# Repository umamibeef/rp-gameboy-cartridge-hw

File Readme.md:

# HW repository for the Croco Cartridges
The files come as is. I used them to order the cartridges, but while ordering yourself you should of course check yourself if everything is correct.

## Revisions
See [CHANGELOG.md](CHANGELOG.md) for what changed in each board revision.

## License
CERN Open Hardware Licence Version 2 - Permissive

## What you should look after while ordering
The PCB thickness should be 0.8mm. This will make perfect contact with the Gameboy if the PCB is within a cartridge casing.

You should order with ENIG (electroless nickel immersion gold) plating. While the cartridge will work with HASL you will getter contact with ENIG and it is less prone to wearing down.

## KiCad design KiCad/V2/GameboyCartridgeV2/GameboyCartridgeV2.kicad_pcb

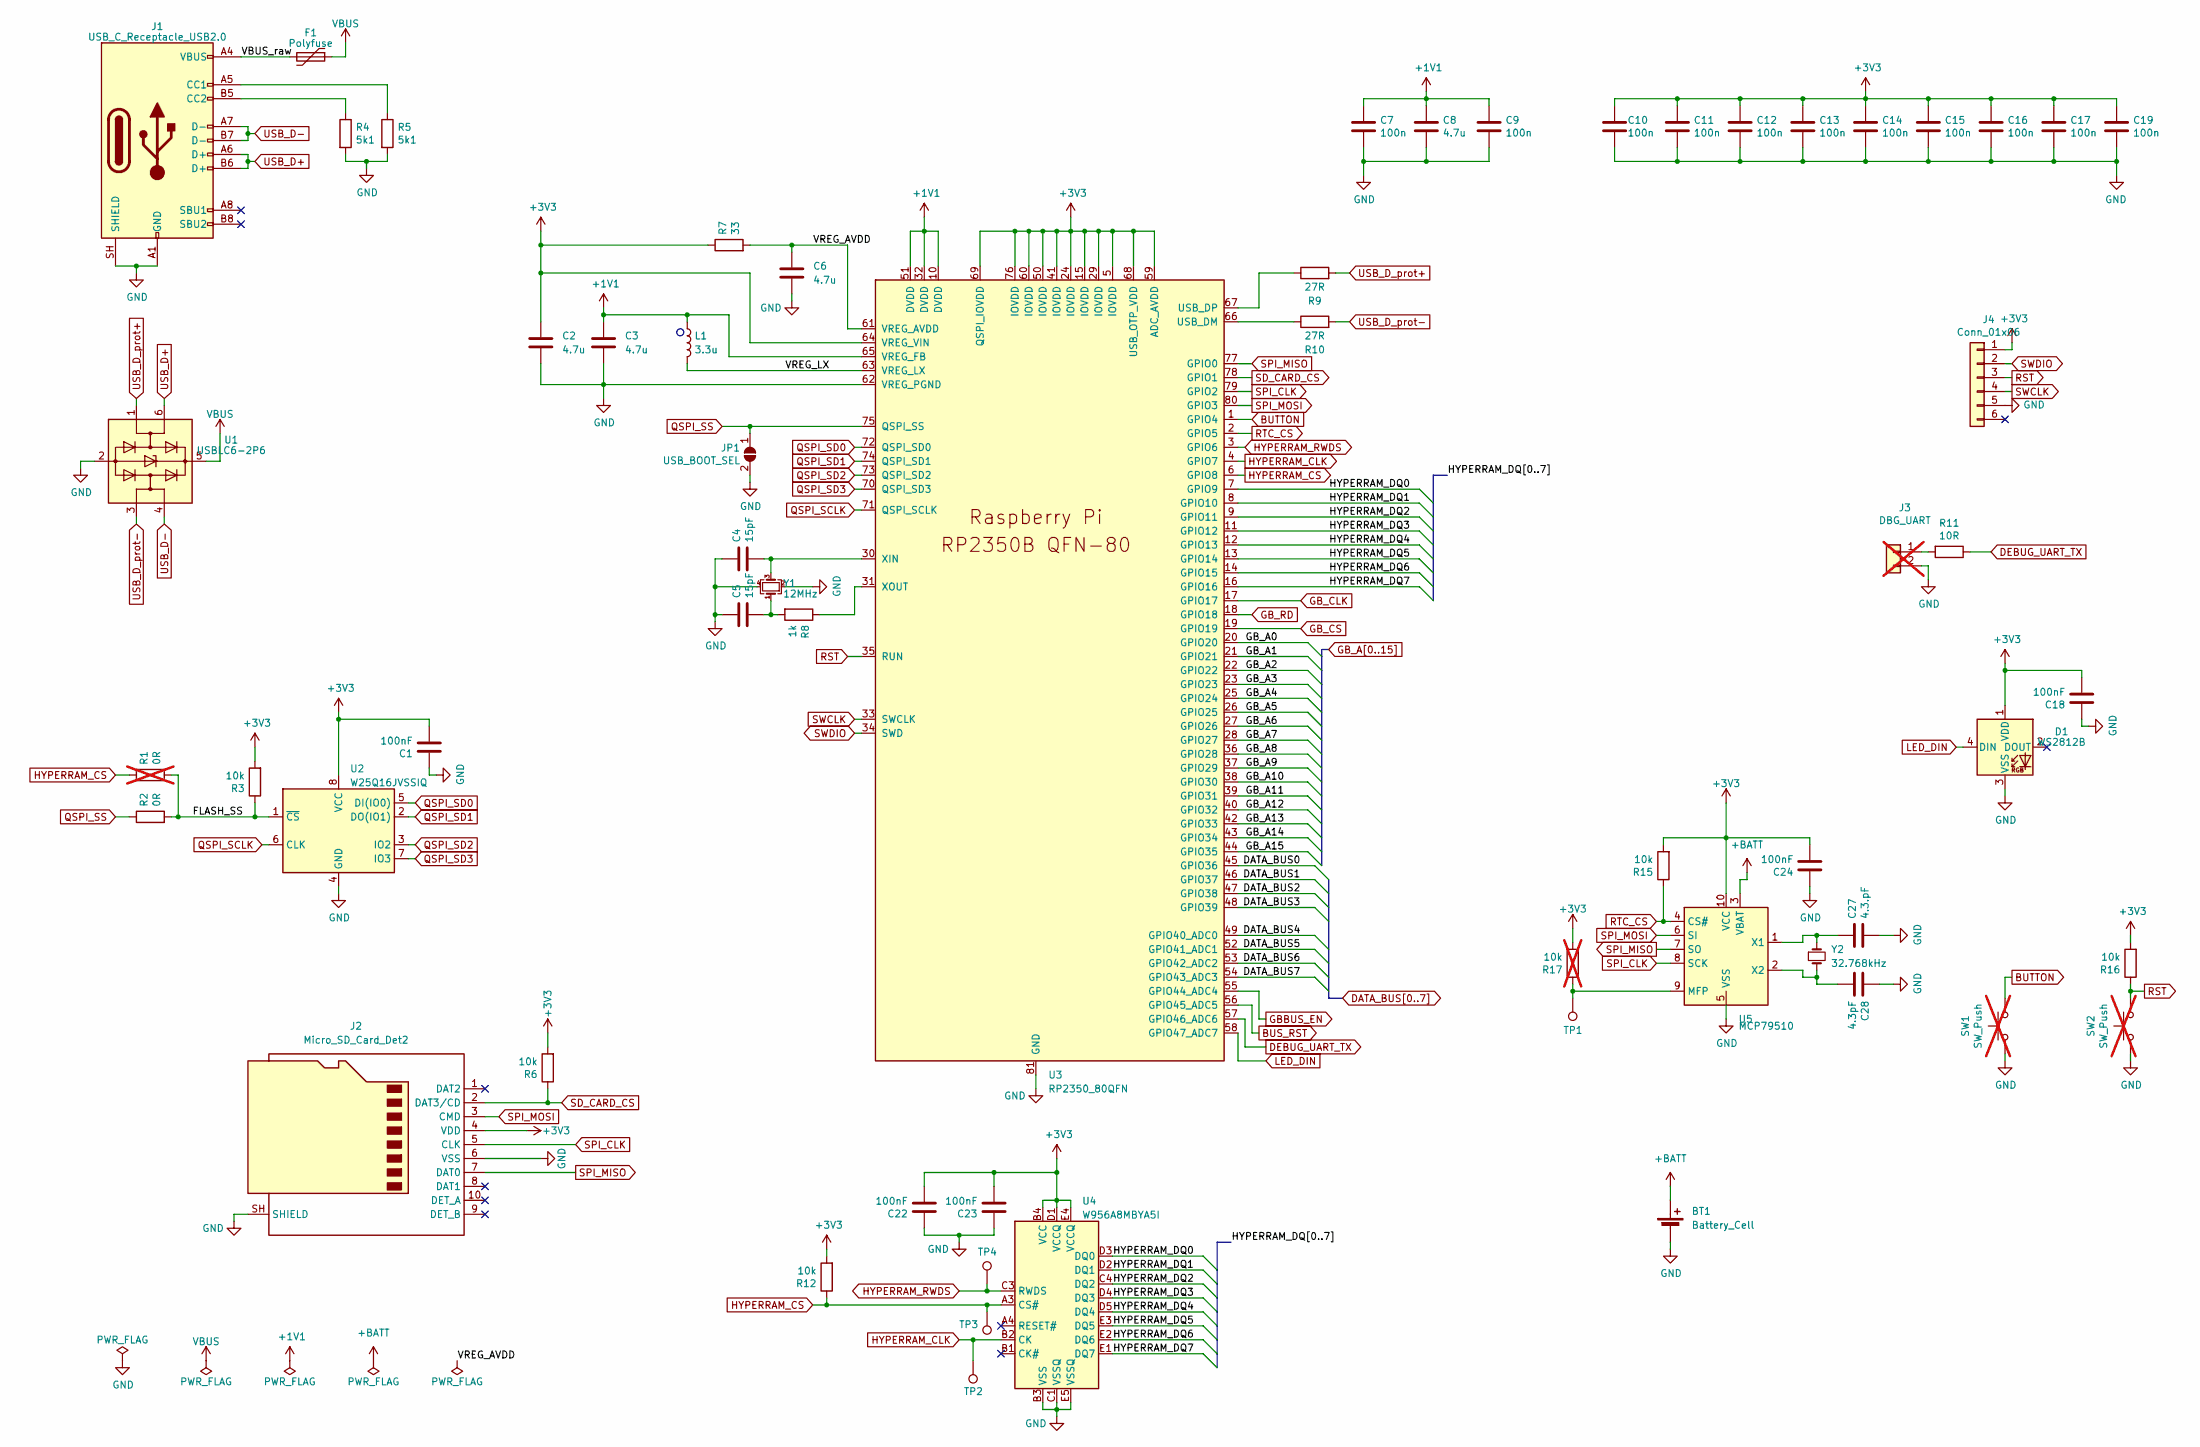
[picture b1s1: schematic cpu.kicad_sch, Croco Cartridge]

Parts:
BT1: Battery_Cell; BatteryHolder_Keystone_3000_1x12mm; LCSC C6997853
C1, C18, C22, C23, C24: 100nF; C_0603_1608Metric
C2, C3: 4.7u; C_0402_1005Metric_small_pads
C4, C5: 15pF; C_0603_1608Metric; LCSC C1644
C6, C8: 4.7u; C_0402_1005Metric
C7, C9, C10, C11, C12, C13, C14, C15, C16, C17, C19: 100n; C_0402_1005Metric
C27: 4.3.pF; C_0603_1608Metric; LCSC C1644
C28: 4.3pF; C_0603_1608Metric; LCSC C1644
D1: WS2812B; LED_WS2812B_PLCC4_5.0x5.0mm_P3.2mm; LCSC C2761795
F1: Polyfuse; Fuse_1206_3216Metric; LCSC C2649911
J1: USB_C_Receptacle_USB2.0; USB_C_Receptacle_GCT_USB4105-xx-A_16P_TopMnt_Horizontal; LCSC C2927037
J2: Micro_SD_Card_Det2; microSD_HC_Hirose_DM3D-SF; LCSC C719027
J3: DBG_UART; PinHeader_1x02_P2.54mm_Horizontal; not fitted
J4: Conn_01x06; Tag-Connect_TC2030-IDC-NL_2x03_P1.27mm_Vertical
JP1: USB_BOOT_SEL; SolderJumper-2_P1.3mm_Open_RoundedPad1.0x1.5mm
L1: 3.3u; L_pol_2016; LCSC C42411119
R1: 0R; R_0603_1608Metric; not fitted
R2: 0R; R_0603_1608Metric
R3, R6, R12, R15, R16: 10k; R_0603_1608Metric
R4, R5: 5k1; R_0603_1608Metric
R7: 33; R_0402_1005Metric
R8: 1k; R_0603_1608Metric
R9, R10: 27R; R_0603_1608Metric
R11: 10R; R_0603_1608Metric
R17: 10k; R_0603_1608Metric; not fitted
SW1: SW_Push; GameBoy_soft_button; not fitted
SW2: SW_Push; SW_SPST_PTS810; not fitted
TP1, TP2, TP3, TP4: TestPoint; TestPoint_Pad_D1.0mm
U1: USBLC6-2P6; SOT-666; LCSC C15999
U2: W25Q16JVSSIQ; SOIC-8_5.3x5.3mm_P1.27mm; LCSC C82317
U3: RP2350_80QFN; RP2350-QFN-80-1EP_10x10_P0.4mm_EP3.4x3.4mm_ThermalVias; LCSC C42415655
U4: W956A8MBYA5I; BGA25C100P5X5_800X600X120N; LCSC C5375118
U5: MCP79510; MSOP-10_3x3mm_P0.5mm; LCSC C627708
Y1: 12MHz; Crystal_SMD_TXC_7M-4Pin_3.2x2.5mm; LCSC C668845
Y2: 32.768kHz; Crystal_SMD_TXC_9HT11-2Pin_2.0x1.2mm; LCSC C97602

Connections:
+1V1: C3.1, C7.1, C8.1, C9.1, L1.1, U3.10 (DVDD), U3.32 (DVDD), U3.51 (DVDD), U3.65 (VREG_FB)
+3V3: C1.2, C2.1, C10.1, C11.1, C12.1, C13.1, C14.1, C15.1, C16.1, C17.1, C18.2, C19.1, C22.2, C23.2, C24.2, D1.1 (VDD), J2.4 (VDD_4), J4.1, R3.2, R6.2, R7.1, R12.2, R15.2, R16.2, R17.2, U2.8 (VCC), U3.5 (IOVDD), U3.15 (IOVDD), U3.24 (IOVDD), U3.29 (IOVDD), U3.41 (IOVDD), U3.50 (IOVDD), U3.59 (ADC_AVDD), U3.60 (IOVDD), U3.64 (VREG_VIN), U3.68 (USB_OTP_VDD), U3.69 (QSPI_IOVDD), U3.76 (IOVDD), U4.B4 (VCC), U4.D1 (VCCQ), U4.E4 (VCCQ), U5.10 (VCC); also elsewhere on the board
+BATT: BT1.1 (+), U5.3 (VBAT)
/CPU/FLASH_SS: R1.2, R2.2, R3.1, U2.1 (~CS)
/CPU/HYPERRAM_DQ0: U3.7 (GPIO9), U4.D3 (DQ0)
/CPU/HYPERRAM_DQ1: U3.8 (GPIO10), U4.D2 (DQ1)
/CPU/HYPERRAM_DQ2: U3.9 (GPIO11), U4.C4 (DQ2)
/CPU/HYPERRAM_DQ3: U3.11 (GPIO12), U4.D4 (DQ3)
/CPU/HYPERRAM_DQ4: U3.12 (GPIO13), U4.D5 (DQ4)
/CPU/HYPERRAM_DQ5: U3.13 (GPIO14), U4.E3 (DQ5)
/CPU/HYPERRAM_DQ6: U3.14 (GPIO15), U4.E2 (DQ6)
/CPU/HYPERRAM_DQ7: U3.16 (GPIO16), U4.E1 (DQ7)
/CPU/VBUS_raw: F1.2, J1.A4 (VBUS_A4), J1.A9 (VBUS_A9), J1.B4 (VBUS_B4), J1.B9 (VBUS_B9)
/CPU/VREG_AVDD: C6.1, R7.2, U3.61 (VREG_AVDD)
/CPU/VREG_LX: L1.2, U3.63 (VREG_LX)
BUS_RST: U3.56 (GPIO45_ADC5); also elsewhere on the board
BUTTON: SW1.1, U3.1 (GPIO4)
DATA_BUS0: U3.45 (GPIO36); also elsewhere on the board
DATA_BUS1: U3.46 (GPIO37); also elsewhere on the board
DATA_BUS2: U3.47 (GPIO38); also elsewhere on the board
DATA_BUS3: U3.48 (GPIO39); also elsewhere on the board
DATA_BUS4: U3.49 (GPIO40_ADC0); also elsewhere on the board
DATA_BUS5: U3.52 (GPIO41_ADC1); also elsewhere on the board
DATA_BUS6: U3.53 (GPIO42_ADC2); also elsewhere on the board
DATA_BUS7: U3.54 (GPIO43_ADC3); also elsewhere on the board
DEBUG_UART_TX: R11.1, U3.57 (GPIO46_ADC6)
GBBUS_EN: U3.55 (GPIO44_ADC4); also elsewhere on the board
GB_A0: U3.20 (GPIO20); also elsewhere on the board
GB_A1: U3.21 (GPIO21); also elsewhere on the board
GB_A2: U3.22 (GPIO22); also elsewhere on the board
GB_A3: U3.23 (GPIO23); also elsewhere on the board
GB_A4: U3.25 (GPIO24); also elsewhere on the board
GB_A5: U3.26 (GPIO25); also elsewhere on the board
GB_A6: U3.27 (GPIO26); also elsewhere on the board
GB_A7: U3.28 (GPIO27); also elsewhere on the board
GB_A8: U3.36 (GPIO28); also elsewhere on the board
GB_A9: U3.37 (GPIO29); also elsewhere on the board
GB_A10: U3.38 (GPIO30); also elsewhere on the board
GB_A11: U3.39 (GPIO31); also elsewhere on the board
GB_A12: U3.40 (GPIO32); also elsewhere on the board
GB_A13: U3.42 (GPIO33); also elsewhere on the board
GB_A14: U3.43 (GPIO34); also elsewhere on the board
GB_A15: U3.44 (GPIO35); also elsewhere on the board
GB_CLK: U3.17 (GPIO17); also elsewhere on the board
GB_CS: U3.19 (GPIO19); also elsewhere on the board
GB_RD: U3.18 (GPIO18); also elsewhere on the board
GND: BT1.2 (-), C1.1, C2.2, C3.2, C4.1, C5.1, C6.2, C7.2, C8.2, C9.2, C10.2, C11.2, C12.2, C13.2, C14.2, C15.2, C16.2, C17.2, C18.1, C19.2, C22.1, C23.1, C24.1, C27.2, C28.1, D1.3 (VSS), J1.A1 (GND_A1), J1.A12 (GND_A12), J1.B1 (GND_B1), J1.B12 (GND_B12), J1.SH (SHIELD_S1), J2.6 (VSS_6), J2.SH (SHIELD_11), J3.2, J4.5, JP1.2 (B), R4.2, R5.2, SW1.2, SW2.2, U1.2 (GND), U2.4 (GND), U3.62 (VREG_PGND), U3.81 (GND), U4.B3 (VSS), U4.C1 (VSSQ), U4.E5 (VSSQ), U5.5 (VSS), Y1.2, Y1.4; also elsewhere on the board
HYPERRAM_CLK: TP2.1 (1_1), U3.4 (GPIO7), U4.B2 (CK)
HYPERRAM_CS: R1.1, R12.1, TP3.1 (1_1), U3.6 (GPIO8), U4.A3 (CS#)
HYPERRAM_RWDS: TP4.1 (1_1), U3.3 (GPIO6), U4.C3 (RWDS)
LED_DIN: D1.4 (DIN), U3.58 (GPIO47_ADC7)
unnamed: C5.2, R8.2, Y1.1
unnamed: J1.A5 (CC1_A5), R5.1
unnamed: J1.B5 (CC2_B5), R4.1
unnamed: J3.1, R11.2
unnamed: R10.1, U3.66 (USB_DM)
unnamed: R9.1, U3.67 (USB_DP)
unnamed: C4.2, U3.30 (XIN), Y1.3
unnamed: R8.1, U3.31 (XOUT)
unnamed: R17.1, TP1.1 (1_1), U5.9 (MFP)
unnamed: C27.1, U5.1 (X1), Y2.1
unnamed: C28.2, U5.2 (X2), Y2.2
QSPI_SCLK: U2.6 (CLK), U3.71 (QSPI_SCLK)
QSPI_SD0: U2.5 (DI(IO0)), U3.72 (QSPI_SD0)
QSPI_SD1: U2.2 (DO(IO1)), U3.74 (QSPI_SD1)
QSPI_SD2: U2.3 (IO2), U3.73 (QSPI_SD2)
QSPI_SD3: U2.7 (IO3), U3.70 (QSPI_SD3)
QSPI_SS: JP1.1 (A), R2.1, U3.75 (QSPI_SS)
RST: J4.3, R16.1, SW2.1, U3.35 (RUN)
RTC_CS: R15.1, U3.2 (GPIO5), U5.4 (CS#)
SD_CARD_CS: J2.2 (DAT3/CD_2), R6.1, U3.78 (GPIO1)
SPI_CLK: J2.5 (CLK_5), U3.79 (GPIO2), U5.8 (SCK)
SPI_MISO: J2.7 (DAT0_7), U3.77 (GPIO0), U5.7 (SO)
SPI_MOSI: J2.3 (CMD_3), U3.80 (GPIO3), U5.6 (SI)
SWCLK: J4.4, U3.33 (SWCLK)
SWDIO: J4.2, U3.34 (SWD)
USB_D+: J1.A6 (D+_A6), J1.B6 (D+_B6), U1.6 (I/O1)
USB_D-: J1.A7 (D-_A7), J1.B7 (D-_B7), U1.4 (I/O2)
USB_D_prot+: R9.2, U1.1 (I/O1)
USB_D_prot-: R10.2, U1.3 (I/O2)
VBUS: F1.1, U1.5 (VBUS); also elsewhere on the board

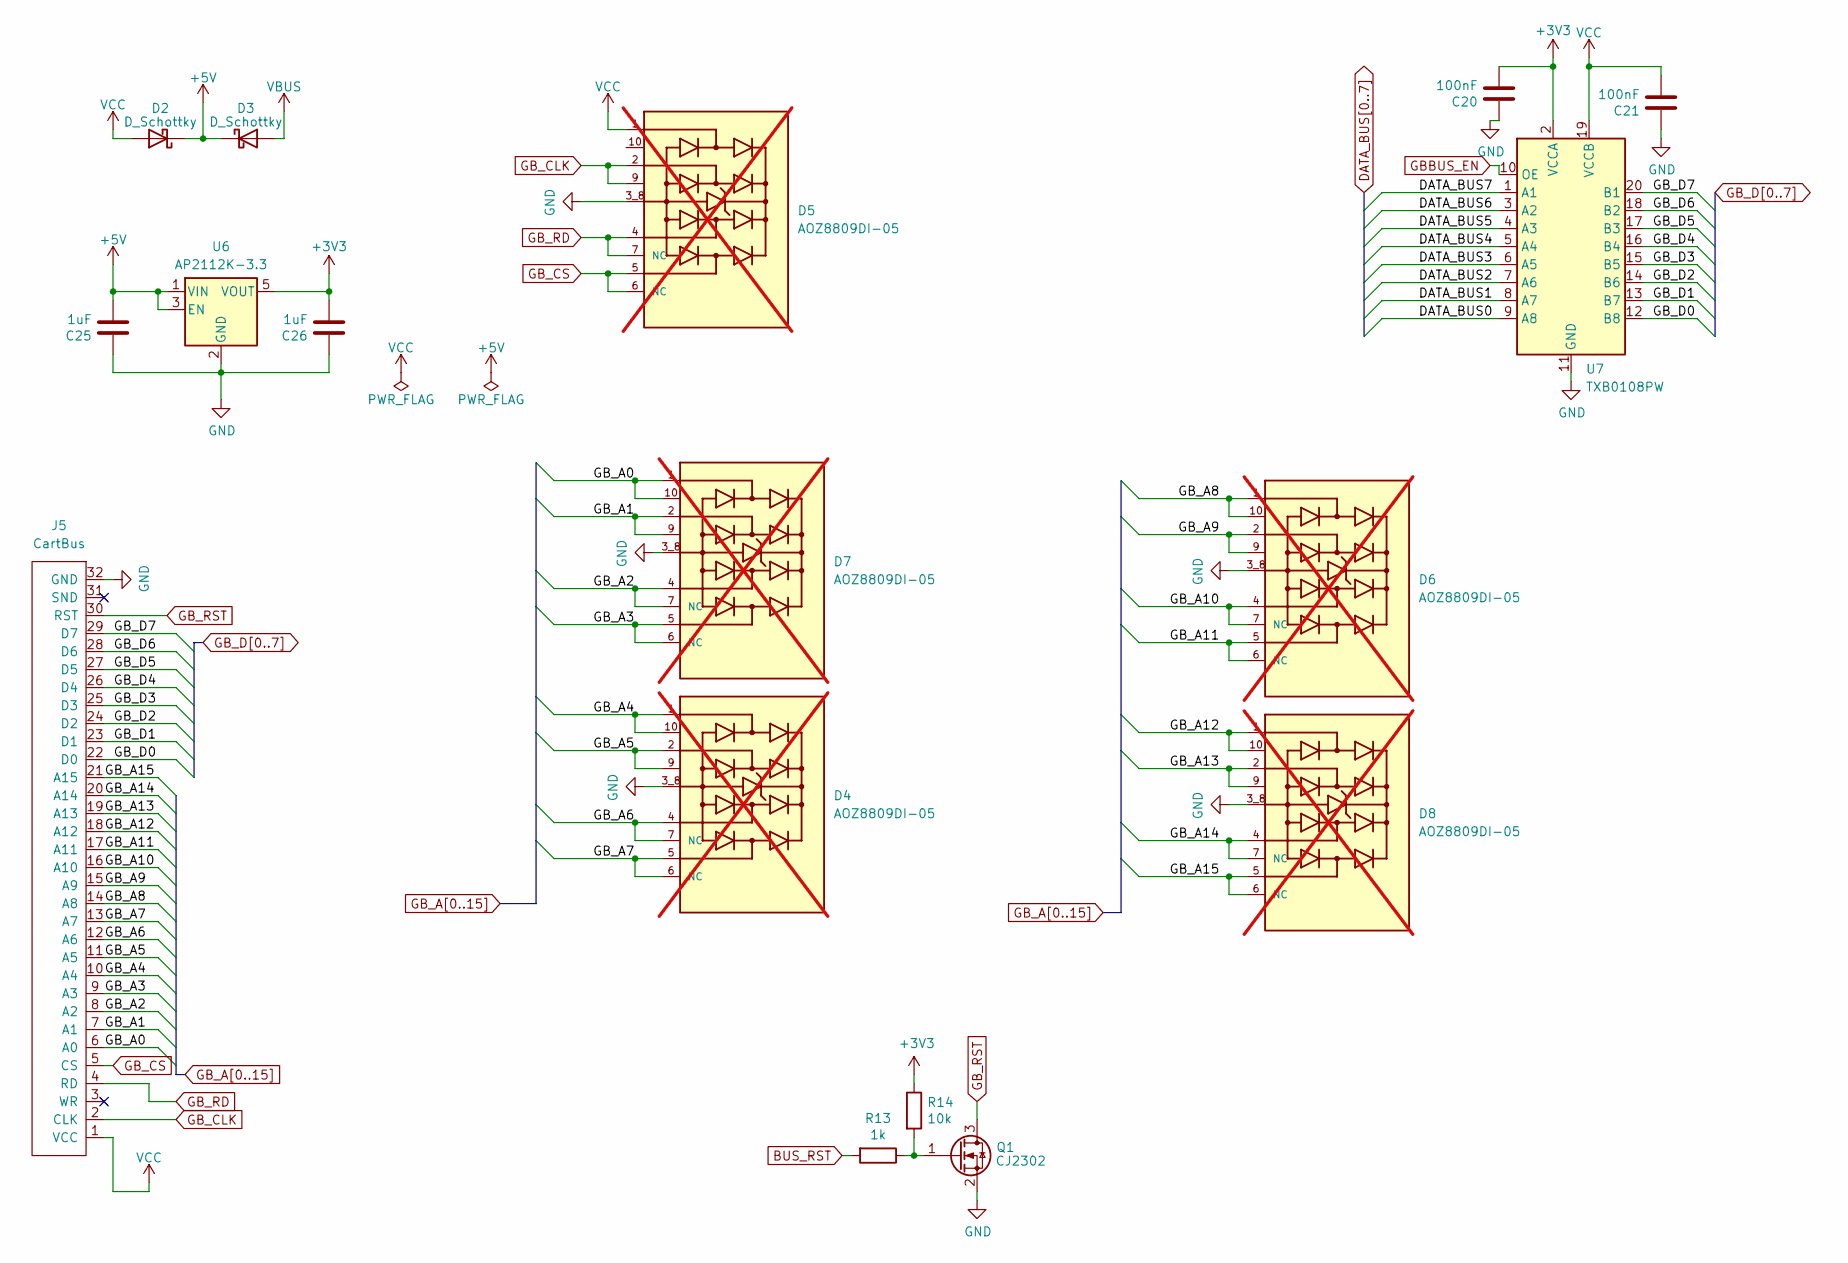
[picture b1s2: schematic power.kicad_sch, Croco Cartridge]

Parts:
C20, C21: 100nF; C_0603_1608Metric
C25, C26: 1uF; C_0603_1608Metric
D2, D3: D_Schottky; D_SOD-123F; LCSC C669022
D4, D5, D6, D7, D8: AOZ8809DI-05; TVS_AOZ8809DI-05; PARTREV Rev. 7.0; not fitted
J5: CartBus; GameBoy_Cartridge_EdgeConnector
Q1: CJ2302; SOT-23; LCSC C8548
R13: 1k; R_0603_1608Metric
R14: 10k; R_0603_1608Metric
U6: AP2112K-3.3; SOT-23-5; LCSC C51118
U7: TXB0108PW; TSSOP-20_4.4x6.5mm_P0.65mm; LCSC C53406

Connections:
+3V3: C20.2, C26.2, R14.1, U6.5 (VOUT), U7.2 (VCCA); also elsewhere on the board
+5V: C25.2, D2.1 (K), D3.1 (K), U6.1 (VIN), U6.3 (EN)
BUS_RST: R13.2; also elsewhere on the board
DATA_BUS0: U7.9 (A8); also elsewhere on the board
DATA_BUS1: U7.8 (A7); also elsewhere on the board
DATA_BUS2: U7.7 (A6); also elsewhere on the board
DATA_BUS3: U7.6 (A5); also elsewhere on the board
DATA_BUS4: U7.5 (A4); also elsewhere on the board
DATA_BUS5: U7.4 (A3); also elsewhere on the board
DATA_BUS6: U7.3 (A2); also elsewhere on the board
DATA_BUS7: U7.1 (A1); also elsewhere on the board
GBBUS_EN: U7.10 (OE); also elsewhere on the board
GB_A0: D7.1, D7.10, J5.6 (A0); also elsewhere on the board
GB_A1: D7.2, D7.9, J5.7 (A1); also elsewhere on the board
GB_A2: D7.4, D7.7 (NC), J5.8 (A2); also elsewhere on the board
GB_A3: D7.5, D7.6 (NC), J5.9 (A3); also elsewhere on the board
GB_A4: D4.1, D4.10, J5.10 (A4); also elsewhere on the board
GB_A5: D4.2, D4.9, J5.11 (A5); also elsewhere on the board
GB_A6: D4.4, D4.7 (NC), J5.12 (A6); also elsewhere on the board
GB_A7: D4.5, D4.6 (NC), J5.13 (A7); also elsewhere on the board
GB_A8: D6.1, D6.10, J5.14 (A8); also elsewhere on the board
GB_A9: D6.2, D6.9, J5.15 (A9); also elsewhere on the board
GB_A10: D6.4, D6.7 (NC), J5.16 (A10); also elsewhere on the board
GB_A11: D6.5, D6.6 (NC), J5.17 (A11); also elsewhere on the board
GB_A12: D8.1, D8.10, J5.18 (A12); also elsewhere on the board
GB_A13: D8.2, D8.9, J5.19 (A13); also elsewhere on the board
GB_A14: D8.4, D8.7 (NC), J5.20 (A14); also elsewhere on the board
GB_A15: D8.5, D8.6 (NC), J5.21 (A15); also elsewhere on the board
GB_CLK: D5.2, D5.9, J5.2 (CLK~); also elsewhere on the board
GB_CS: D5.5, D5.6 (NC), J5.5 (CS); also elsewhere on the board
GB_D0: J5.22 (D0), U7.12 (B8)
GB_D1: J5.23 (D1), U7.13 (B7)
GB_D2: J5.24 (D2), U7.14 (B6)
GB_D3: J5.25 (D3), U7.15 (B5)
GB_D4: J5.26 (D4), U7.16 (B4)
GB_D5: J5.27 (D5), U7.17 (B3)
GB_D6: J5.28 (D6), U7.18 (B2)
GB_D7: J5.29 (D7), U7.20 (B1)
GB_RD: D5.4, D5.7 (NC), J5.4 (RD); also elsewhere on the board
GB_RST: J5.30 (RST), Q1.3 (D)
GND: C20.1, C21.1, C25.1, C26.1, D4.3_8, D5.3_8, D6.3_8, D7.3_8, D8.3_8, J5.32 (GND), Q1.2 (S), U6.2 (GND), U7.11 (GND); also elsewhere on the board
unnamed: Q1.1 (G), R13.1, R14.2
VBUS: D3.2 (A); also elsewhere on the board
VCC: C21.2, D2.2 (A), D5.1, J5.1 (VCC), U7.19 (VCCB)

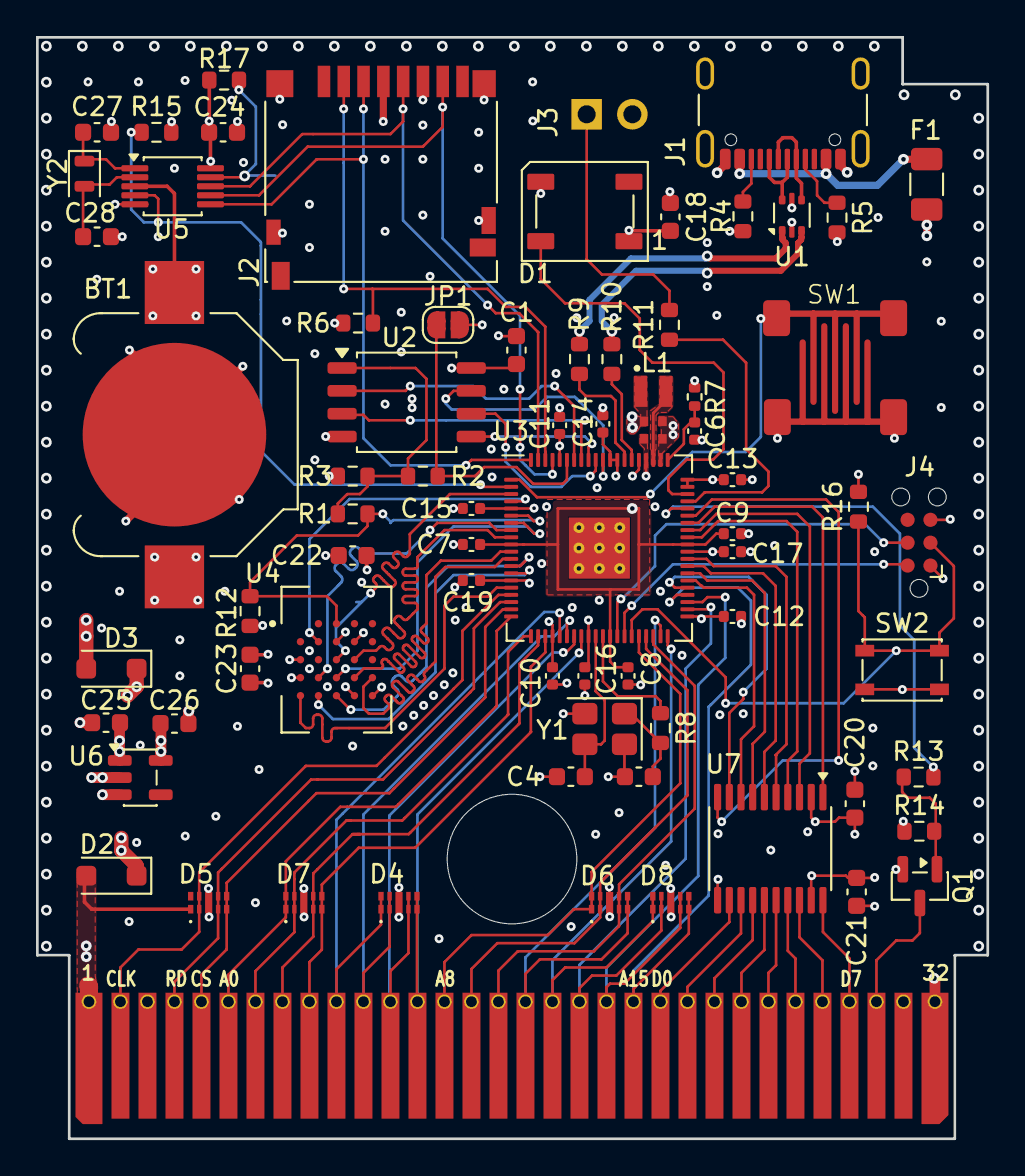
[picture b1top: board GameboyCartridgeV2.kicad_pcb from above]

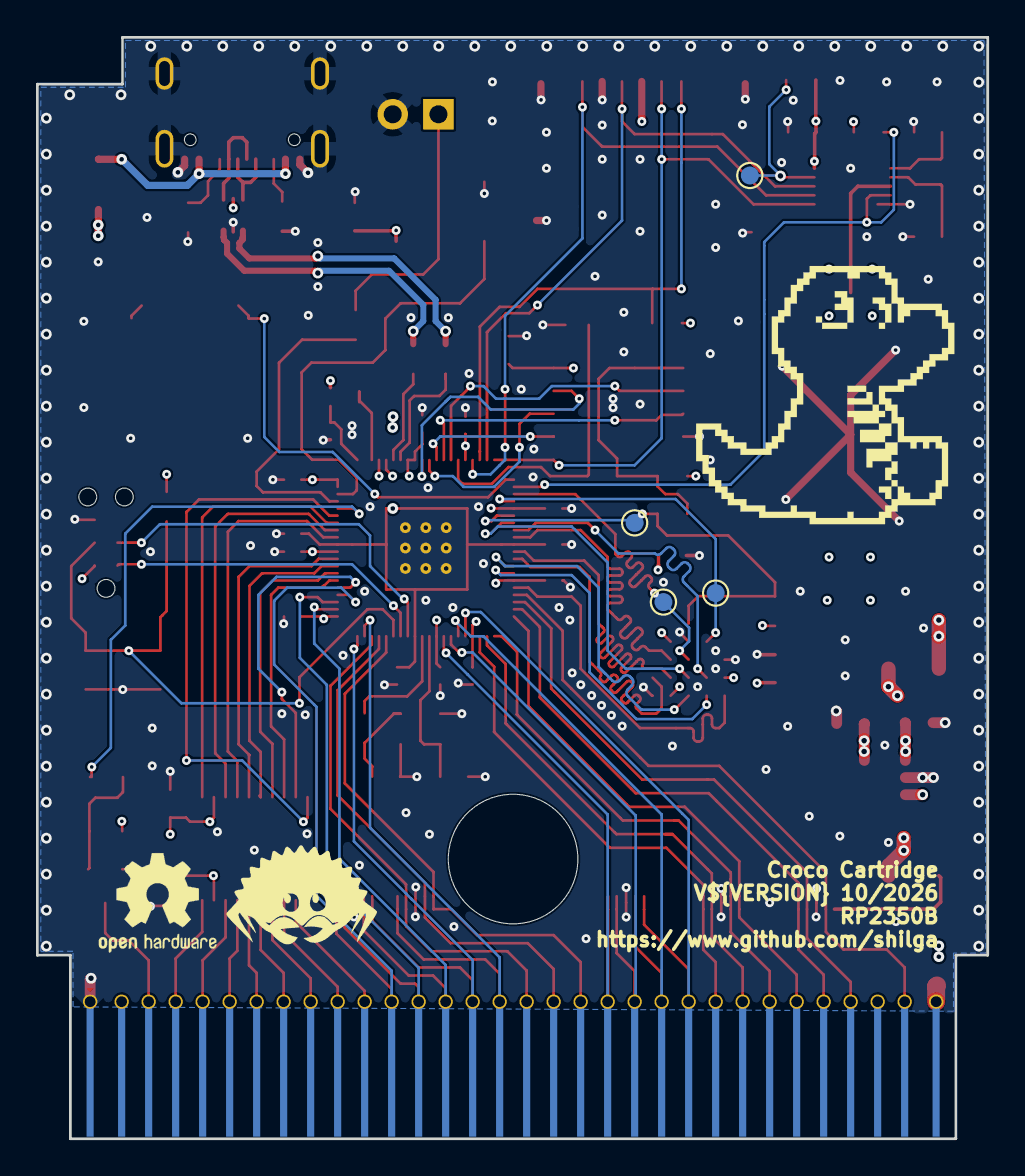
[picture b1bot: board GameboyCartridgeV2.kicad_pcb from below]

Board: 4 copper layers, 52.8 x 61.2 mm, 78 parts (4 on the bottom side), 93 nets.

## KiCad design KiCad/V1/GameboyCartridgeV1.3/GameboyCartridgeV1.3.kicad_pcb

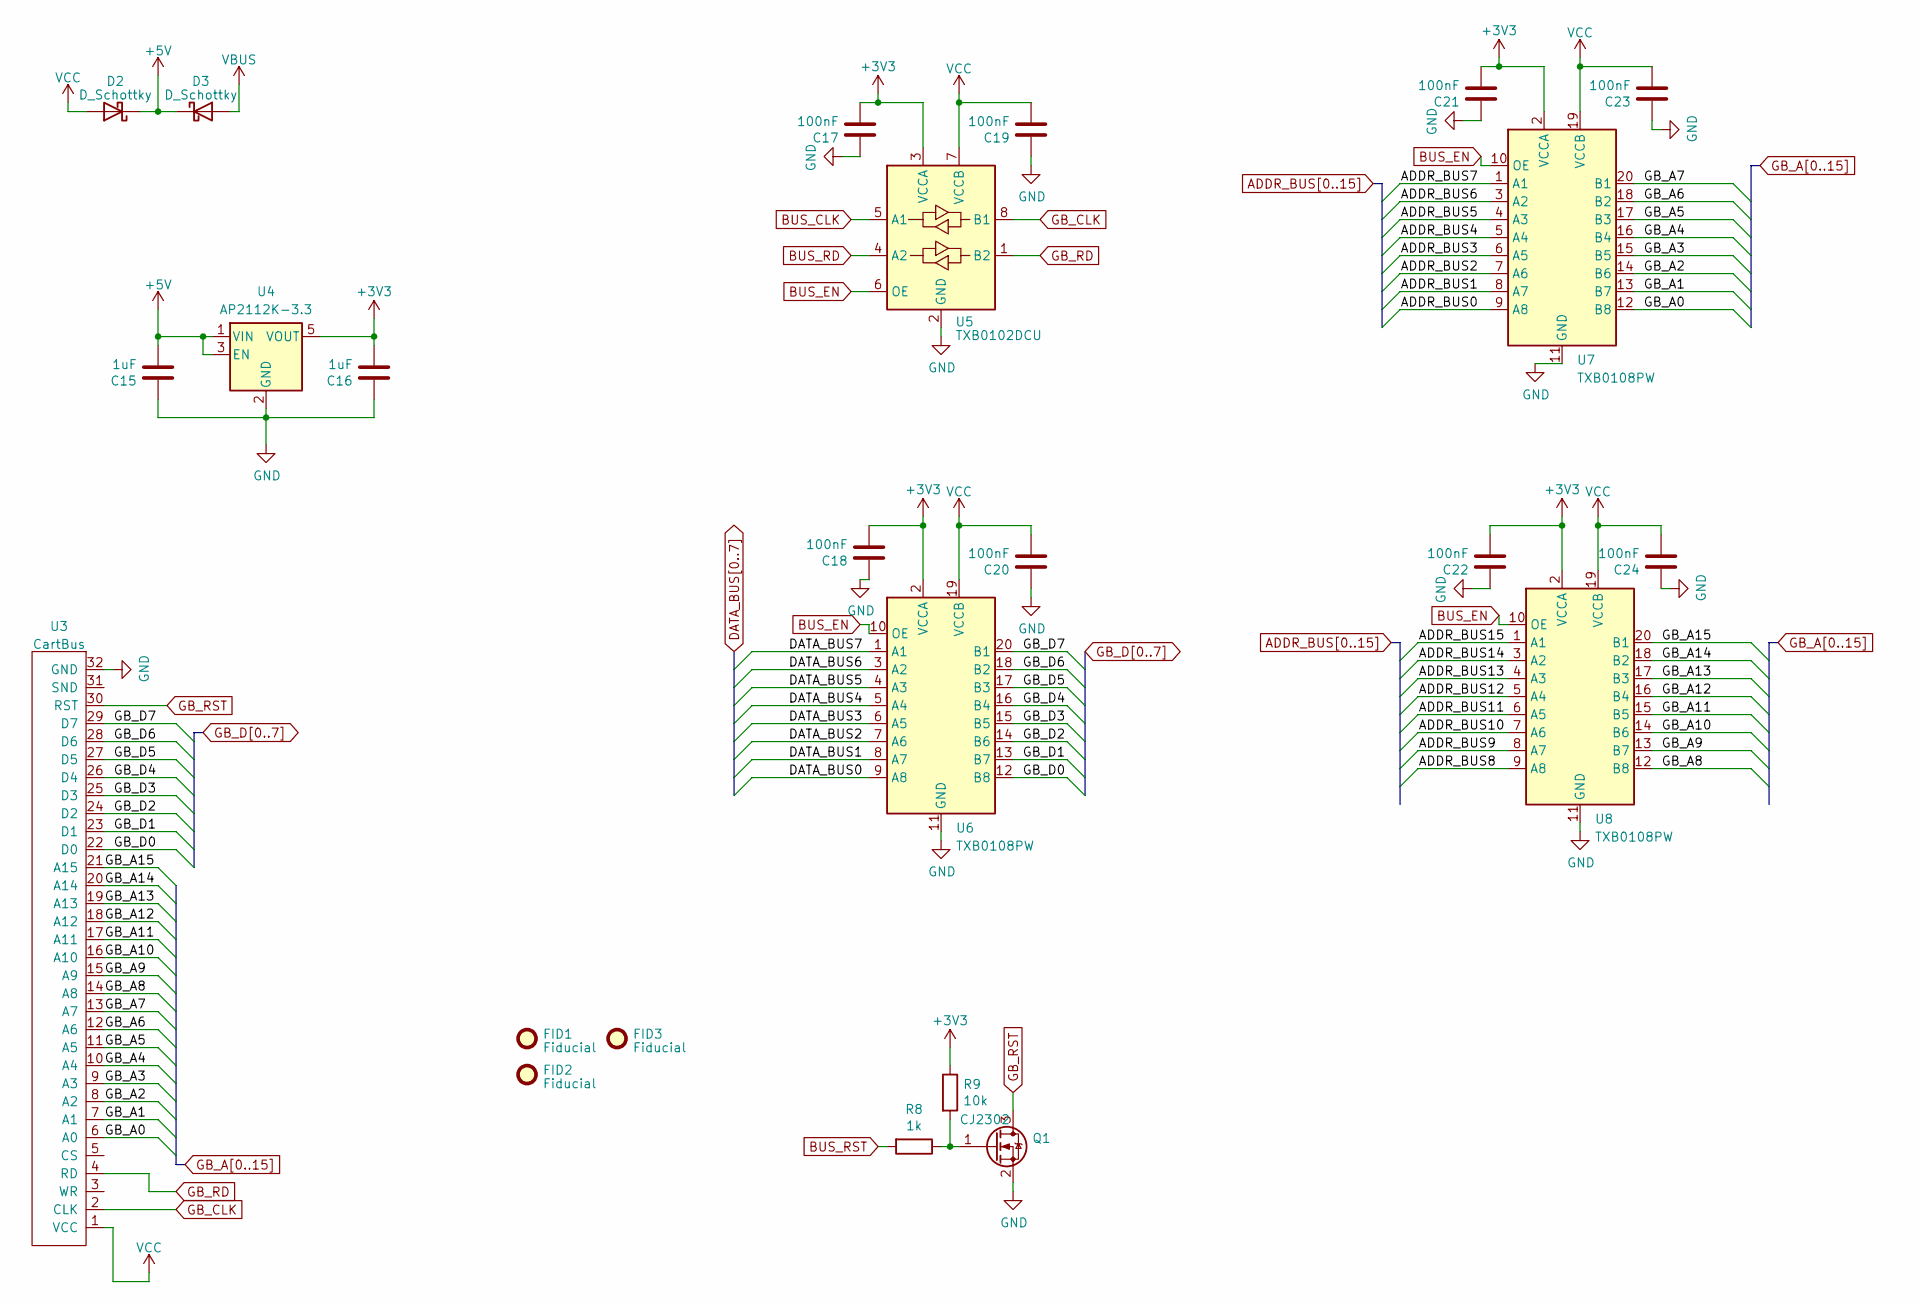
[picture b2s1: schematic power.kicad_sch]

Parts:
C15, C16: 1uF; C_0603_1608Metric
C17, C18, C19, C20, C21, C22, C23, C24: 100nF; C_0603_1608Metric_Pad1.08x0.95mm_HandSolder
D2, D3: D_Schottky; D_SOD-123F; LCSC C669022
FID1, FID2, FID3: Fiducial; Fiducial_1mm_Mask2mm
Q1: CJ2302; SOT-23; LCSC C8548
R8: 1k; R_0603_1608Metric_Pad0.98x0.95mm_HandSolder
R9: 10k; R_0603_1608Metric_Pad0.98x0.95mm_HandSolder
U3: CartBus; GameBoy_Cartridge_EdgeConnector
U4: AP2112K-3.3; SOT-23-5; LCSC C51118
U5: TXB0102DCU; VSSOP-8_2.4x2.1mm_P0.5mm; LCSC C60709
U6, U7, U8: TXB0108PW; TSSOP-20_4.4x6.5mm_P0.65mm; LCSC C53406

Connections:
+3V3: C16.2, C17.2, C18.2, C21.2, C22.2, R9.1, U4.5 (VOUT), U5.3 (VCCA), U6.2 (VCCA), U7.2 (VCCA), U8.2 (VCCA); also elsewhere on the board
+5V: C15.2, D2.1 (K), D3.1 (K), U4.1 (VIN), U4.3 (EN)
ADDR_BUS0: U7.9 (A8); also elsewhere on the board
ADDR_BUS1: U7.8 (A7); also elsewhere on the board
ADDR_BUS2: U7.7 (A6); also elsewhere on the board
ADDR_BUS3: U7.6 (A5); also elsewhere on the board
ADDR_BUS4: U7.5 (A4); also elsewhere on the board
ADDR_BUS5: U7.4 (A3); also elsewhere on the board
ADDR_BUS6: U7.3 (A2); also elsewhere on the board
ADDR_BUS7: U7.1 (A1); also elsewhere on the board
ADDR_BUS8: U8.9 (A8); also elsewhere on the board
ADDR_BUS9: U8.8 (A7); also elsewhere on the board
ADDR_BUS10: U8.7 (A6); also elsewhere on the board
ADDR_BUS11: U8.6 (A5); also elsewhere on the board
ADDR_BUS12: U8.5 (A4); also elsewhere on the board
ADDR_BUS13: U8.4 (A3); also elsewhere on the board
ADDR_BUS14: U8.3 (A2); also elsewhere on the board
ADDR_BUS15: U8.1 (A1); also elsewhere on the board
BUS_CLK: U5.5 (A1); also elsewhere on the board
BUS_EN: U5.6 (OE), U6.10 (OE), U7.10 (OE), U8.10 (OE); also elsewhere on the board
BUS_RD: U5.4 (A2); also elsewhere on the board
BUS_RST: R8.2; also elsewhere on the board
DATA_BUS0: U6.9 (A8); also elsewhere on the board
DATA_BUS1: U6.8 (A7); also elsewhere on the board
DATA_BUS2: U6.7 (A6); also elsewhere on the board
DATA_BUS3: U6.6 (A5); also elsewhere on the board
DATA_BUS4: U6.5 (A4); also elsewhere on the board
DATA_BUS5: U6.4 (A3); also elsewhere on the board
DATA_BUS6: U6.3 (A2); also elsewhere on the board
DATA_BUS7: U6.1 (A1); also elsewhere on the board
GB_A0: U3.6 (A0), U7.12 (B8)
GB_A1: U3.7 (A1), U7.13 (B7)
GB_A2: U3.8 (A2), U7.14 (B6)
GB_A3: U3.9 (A3), U7.15 (B5)
GB_A4: U3.10 (A4), U7.16 (B4)
GB_A5: U3.11 (A5), U7.17 (B3)
GB_A6: U3.12 (A6), U7.18 (B2)
GB_A7: U3.13 (A7), U7.20 (B1)
GB_A8: U3.14 (A8), U8.12 (B8)
GB_A9: U3.15 (A9), U8.13 (B7)
GB_A10: U3.16 (A10), U8.14 (B6)
GB_A11: U3.17 (A11), U8.15 (B5)
GB_A12: U3.18 (A12), U8.16 (B4)
GB_A13: U3.19 (A13), U8.17 (B3)
GB_A14: U3.20 (A14), U8.18 (B2)
GB_A15: U3.21 (A15), U8.20 (B1)
GB_CLK: U3.2 (CLK~), U5.8 (B1)
GB_D0: U3.22 (D0), U6.12 (B8)
GB_D1: U3.23 (D1), U6.13 (B7)
GB_D2: U3.24 (D2), U6.14 (B6)
GB_D3: U3.25 (D3), U6.15 (B5)
GB_D4: U3.26 (D4), U6.16 (B4)
GB_D5: U3.27 (D5), U6.17 (B3)
GB_D6: U3.28 (D6), U6.18 (B2)
GB_D7: U3.29 (D7), U6.20 (B1)
GB_RD: U3.4 (RD), U5.1 (B2)
GB_RST: Q1.3 (D), U3.30 (RST)
GND: C15.1, C16.1, C17.1, C18.1, C19.1, C20.1, C21.1, C22.1, C23.1, C24.1, Q1.2 (S), U3.32 (GND), U4.2 (GND), U5.2 (GND), U6.11 (GND), U7.11 (GND), U8.11 (GND); also elsewhere on the board
unnamed: Q1.1 (G), R8.1, R9.2
VBUS: D3.2 (A); also elsewhere on the board
VCC: C19.2, C20.2, C23.2, C24.2, D2.2 (A), U3.1 (VCC), U5.7 (VCCB), U6.19 (VCCB), U7.19 (VCCB), U8.19 (VCCB)
